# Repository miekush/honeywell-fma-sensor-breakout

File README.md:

# Honeywell FMA MicroForce Sensor Breakout

Simple breakout PCB for Honeywell FMA MicroForce series force sensors

# Interface Selection

As the breakout supports both SPI and I2C variants of the MicroForce sensors, there are some optional components that may or may not need to be fitted. See below table.

| Component  | SPI | I2C | 
| :---: | :---: | :---: |
| C1 | 1uF | 1uF |
| C2 | 0.1uF | 0.1uF |
| R1 | - | 10k |
| R2 | - | 10k |
| R3 | 10k | - |

# License

MKE supports the open source hardware community by sharing hardware design files freely on GitHub!

Please support MKE by purchasing products on [Tindie](https://www.tindie.com/stores/mkengineering/)!

Designed by Mike Kushnerik (miekush)

Licensed under [Creative Commons Attribution-ShareAlike CC BY-SA 4.0](http://creativecommons.org/licenses/by-sa/4.0/)

All text above must be included in any redistribution!

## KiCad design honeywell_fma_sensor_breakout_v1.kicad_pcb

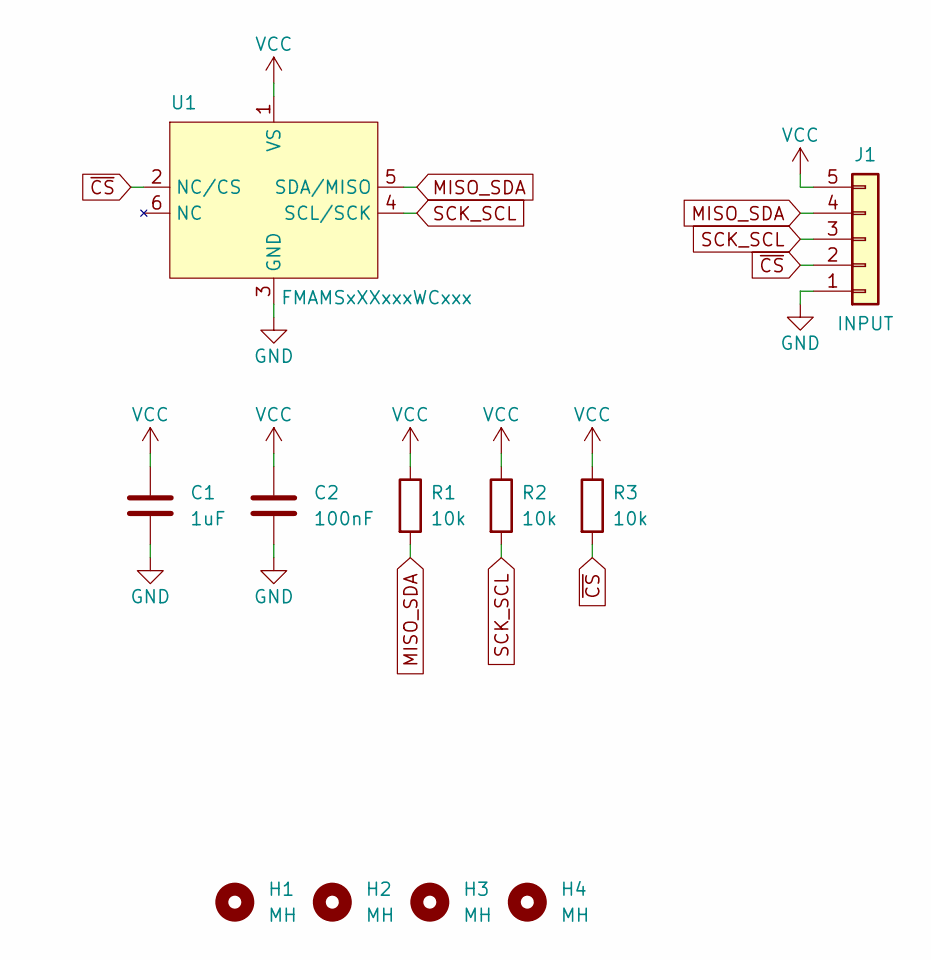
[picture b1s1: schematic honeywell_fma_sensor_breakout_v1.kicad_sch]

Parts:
C1: 1uF; C_0603_1608Metric
C2: 100nF; C_0603_1608Metric
H1, H2, H3, H4: MH; MountingHole_2.2mm_M2
J1: INPUT; PinHeader_1x05_P2.54mm_Vertical
R1, R2, R3: 10k; R_0603_1608Metric
U1: FMAMSxXXxxxWCxxx

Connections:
GND: C1.2, C2.2, J1.1, U1.3 (GND)
MISO_SDA: J1.4, R1.2, U1.5 (SDA/MISO)
SCK_SCL: J1.3, R2.2, U1.4 (SCL/SCK)
VCC: C1.1, C2.1, J1.5, R1.1, R2.1, R3.1, U1.1 (VS)
~CS: J1.2, R3.2, U1.2 (NC/CS)

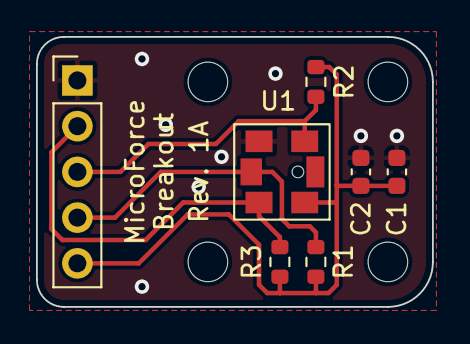
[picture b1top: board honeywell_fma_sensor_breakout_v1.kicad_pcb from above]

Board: 2 copper layers, 22.0 x 15.0 mm, 11 parts (0 on the bottom side), 5 nets.

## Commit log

2022-10-06 Initial upload
2022-10-08 Add images
